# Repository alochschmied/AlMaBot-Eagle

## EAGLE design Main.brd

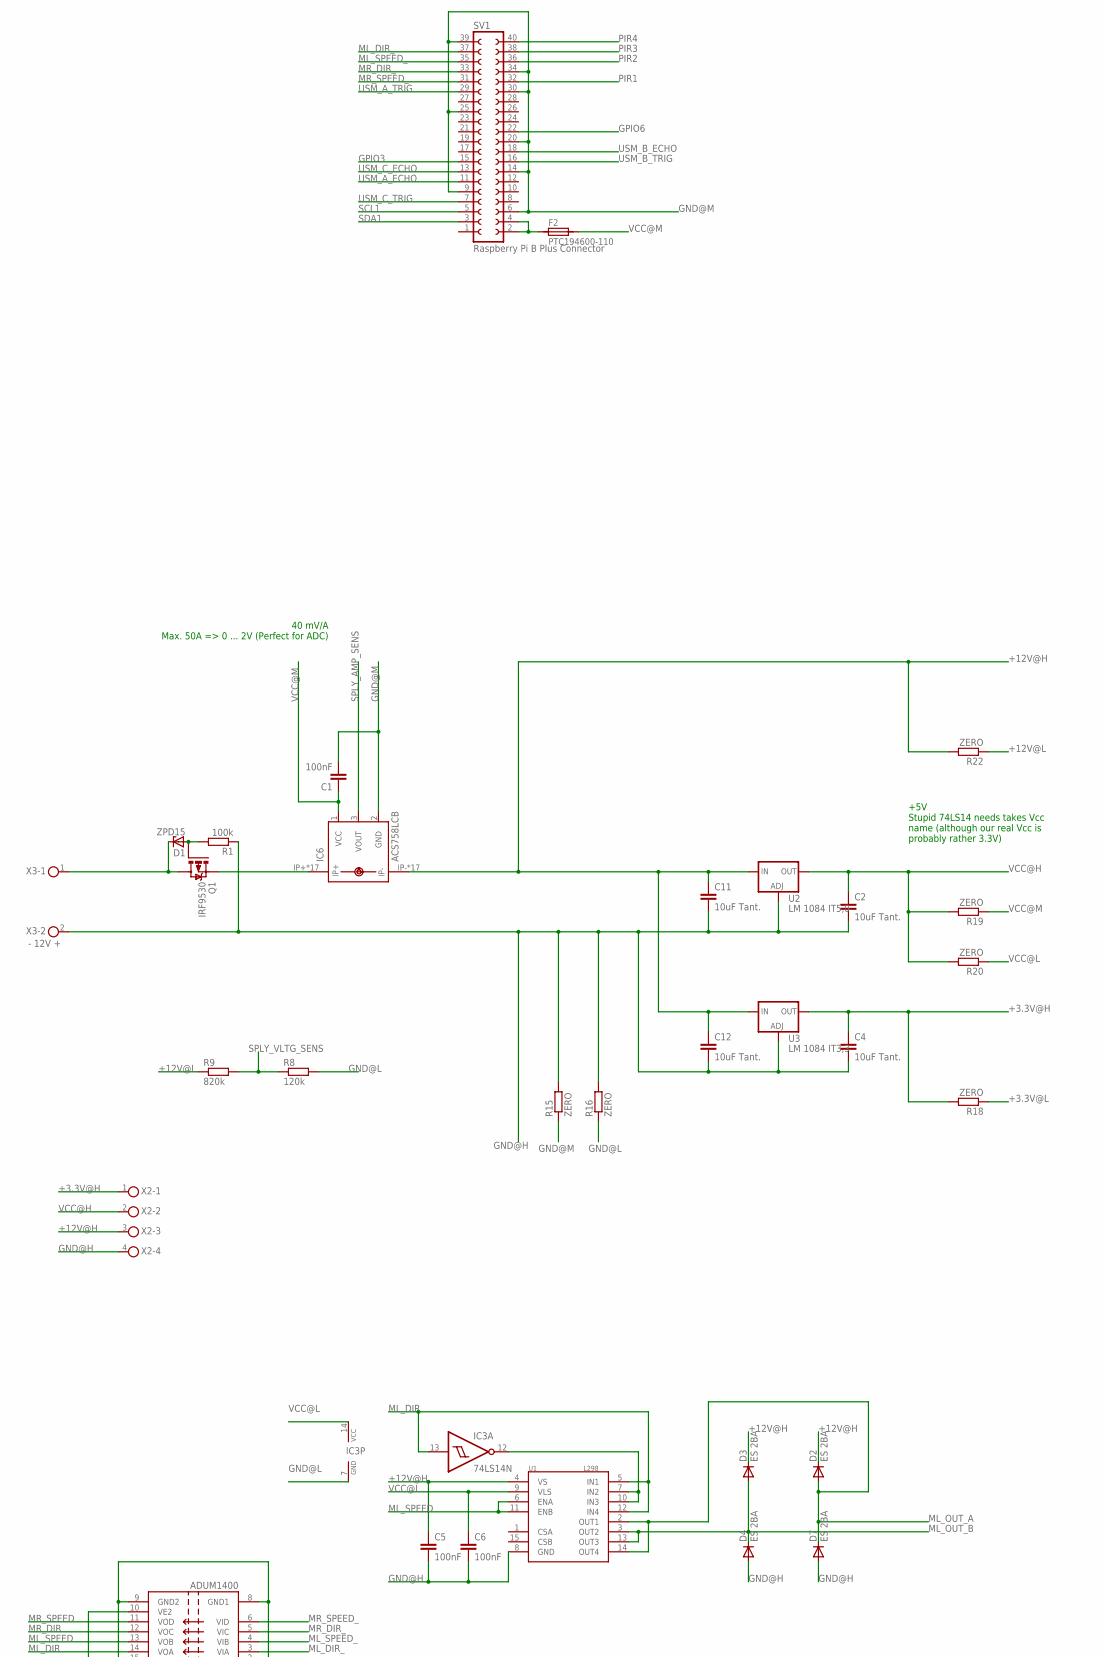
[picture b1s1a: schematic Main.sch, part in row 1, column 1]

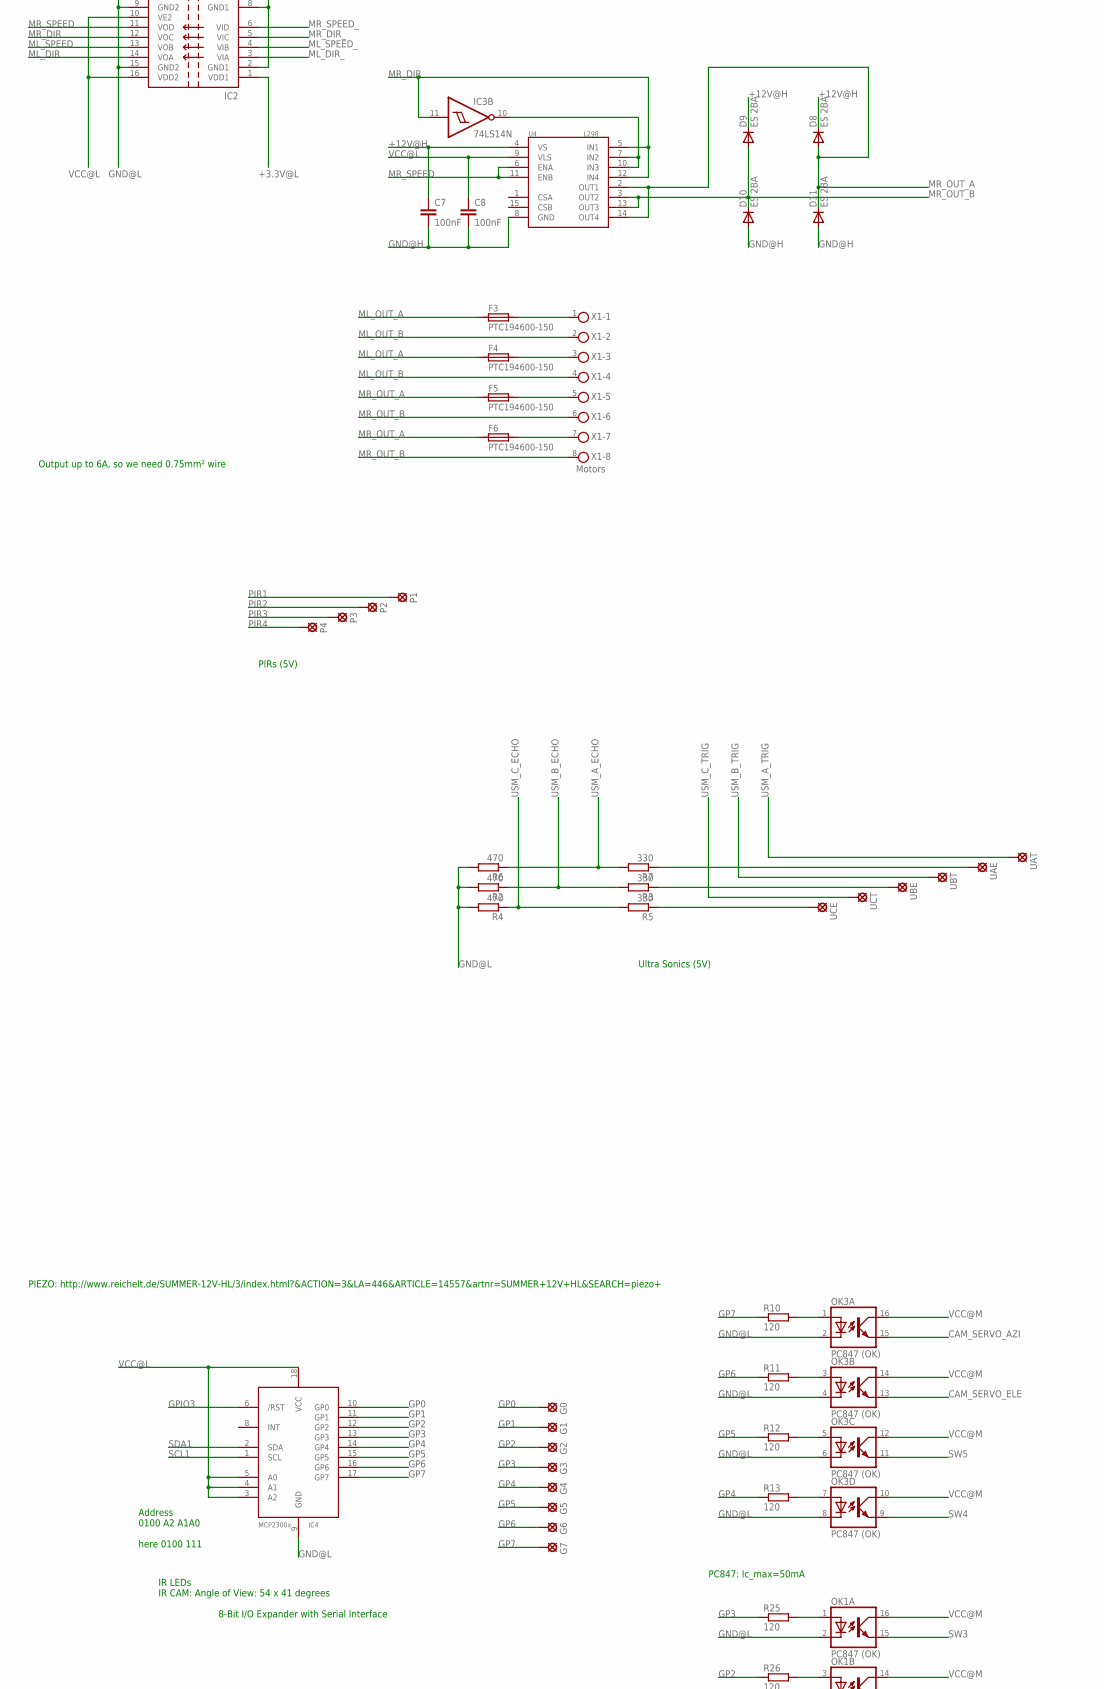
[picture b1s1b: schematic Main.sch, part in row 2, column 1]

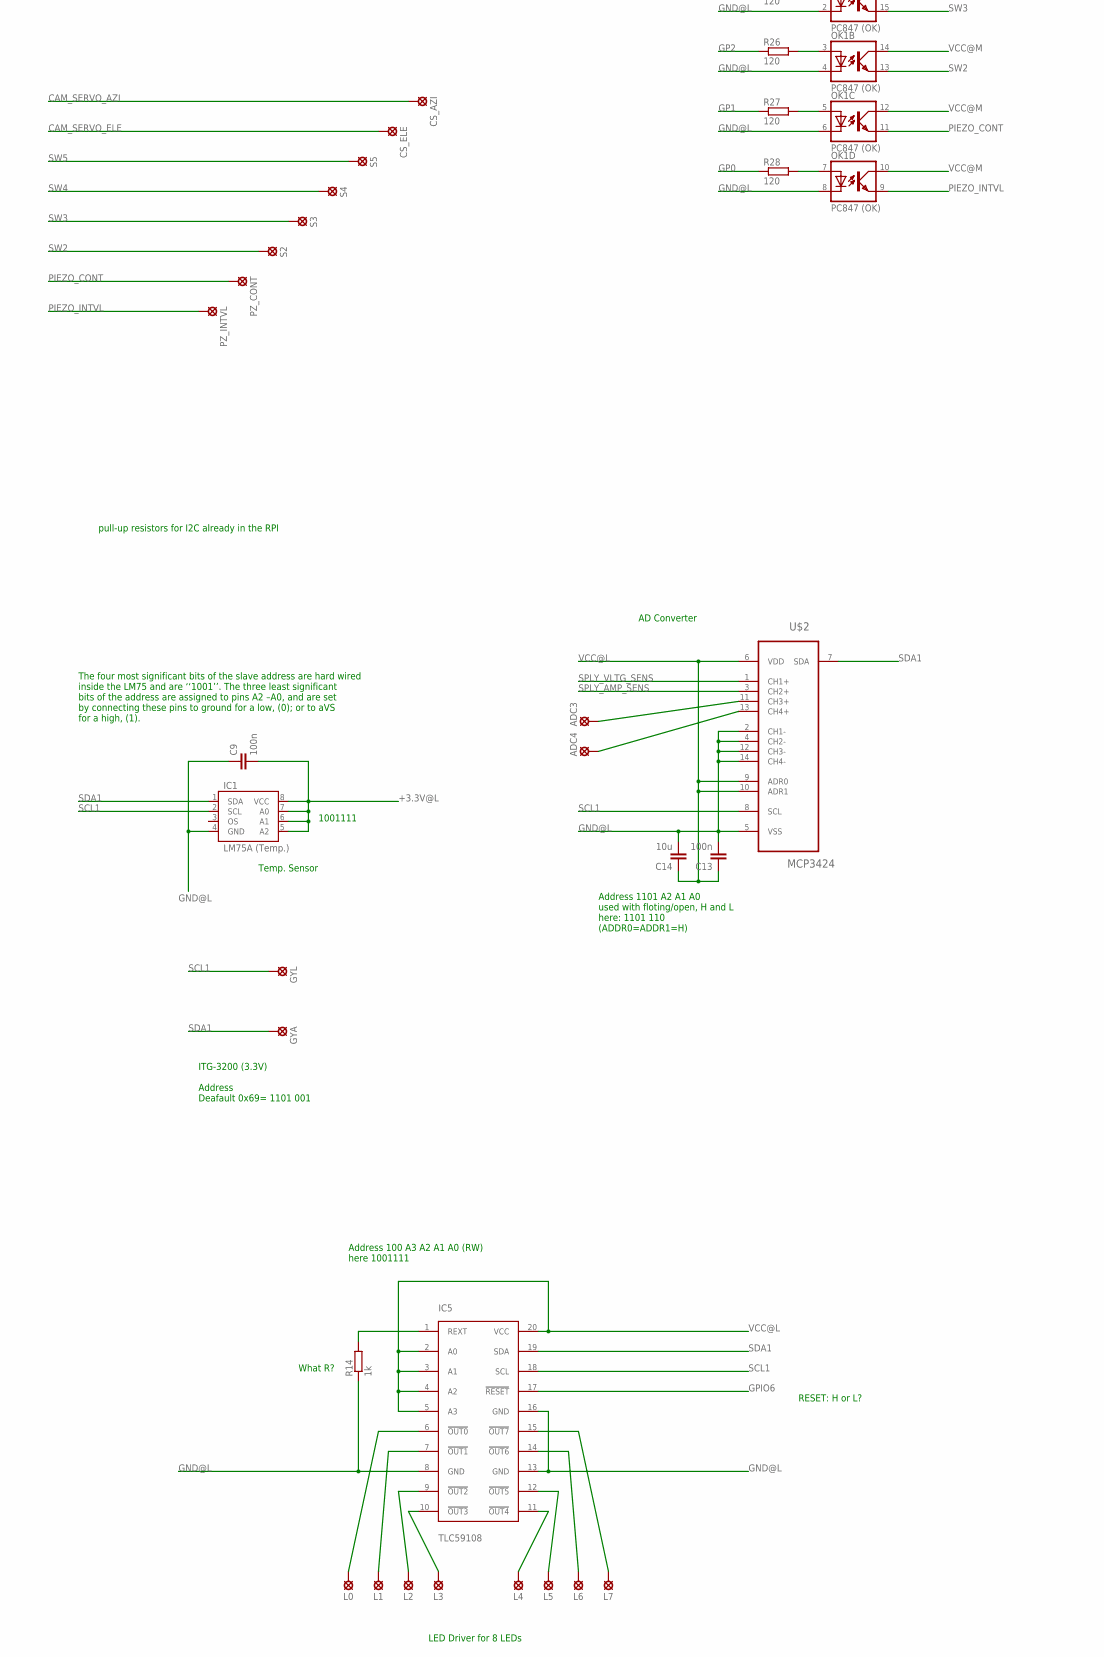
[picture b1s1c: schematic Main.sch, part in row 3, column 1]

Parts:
ADC3, ADC4: LSP10
C1, C5, C6, C7, C8: 100nF; C0805
C2, C4, C11, C12: 10uF Tant.; C025-040X050
C9, C13: 100n; C0805
C14: 10u; C0805
CS_AZI: LSP10
CS_ELE: LSP10
D1: ZPD15; DO35Z10
D2, D3, D4, D7, D8, D9, D10, D11: ES 2BA; SMB
F2: PTC194600-110; 1820
F3, F4, F5, F6: PTC194600-150; 1820
G0, G1, G2, G3, G4, G5, G6, G7: LSP10
GYA: LSP10
GYL: GYRO_SCL; LSP10
IC1: LM75A (Temp.); SO8
IC2: ADUM1400; SO16W
IC3: 74LS14N; DIL14
IC4: MCP2300X/P; DIL18
IC5: TLC59108; TSSOP20
IC6: ACS758LCB; CB-PFF
L0, L1, L2, L3, L4, L5, L6, L7: LSP10
OK1, OK3: PC847 (OK); DIL16
P1, P2, P3, P4: LSP10
PZ_CONT: LSP10
PZ_INTVL: LSP10
Q1: IRF9530; TO220BV
R1: 100k; R0805
R2, R4, R6: 470; R0603
R3, R5, R7: 330; R0603
R8: 120k; R0603
R9: 820k; R0603
R10, R11, R12, R13, R25, R26, R27, R28: 120; R0603
R14: 1k; R0603
R15, R16, R18, R19, R20, R22: ZERO; 0204V
S2, S3, S4, S5: LSP10
SV1: Raspberry Pi B Plus Connector; FE20-2
U1, U4: L298; MULTIWATT15
U2: LM 1084 IT5,0; 317TS
U3: LM 1084 IT3,3; 317TS
U$2: MCP3424; SOP65P640X120-14N
UAE: LSP10
UAT: LSP10
UBE: LSP10
UBT: LSP10
UCE: LSP10
UCT: LSP10
X1: Motors; 8POL35
X2: AKL59-04; 4POL35
X3: - 12V +; 2POL35

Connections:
+3.3V@H: C4.1, R18.2, U3.2 (OUT), X2.1
+3.3V@L: C9.2, IC1.5 (A2), IC1.6 (A1), IC1.7 (A0), IC1.8 (VCC), IC2.1 (VDD1), R18.1
+12V@H: C5.1, C7.1, C11.1, C12.1, D2.C, D3.C, D8.C, D9.C, IC6.IP-, IC6.IP-@2 (IP-), IC6.IP-@3 (IP-), IC6.IP-@4 (IP-), IC6.IP-@5 (IP-), IC6.IP-@6 (IP-), IC6.IP-@7 (IP-), IC6.IP-@8 (IP-), IC6.IP-@9 (IP-), IC6.IP-@10 (IP-), IC6.IP-@11 (IP-), IC6.IP-@12 (IP-), IC6.IP-@13 (IP-), IC6.IP-@14 (IP-), IC6.IP-@15 (IP-), IC6.IP-@16 (IP-), IC6.IP-@17 (IP-), R22.2, U1.4 (VS), U2.3 (IN), U3.3 (IN), U4.4 (VS), X2.3
+12V@L: R9.1, R22.1
CAM_SERVO_AZI: CS_AZI.MP, OK3.15 (EMIT)
CAM_SERVO_ELE: CS_ELE.MP, OK3.13 (EMIT)
GND@H: C2.2, C4.2, C5.2, C6.2, C7.2, C8.2, C11.2, C12.2, D4.A, D7.A, D10.A, D11.A, R1.1, R15.2, R16.2, U1.8 (GND), U2.1 (ADJ), U3.1 (ADJ), U4.8 (GND), X2.4, X3.2
GND@L: C9.1, C13.2, C14.2, IC1.4 (GND), IC2.2 (GND1), IC2.8 (GND1), IC2.9 (GND2), IC2.15 (GND2), IC3.7 (GND), IC4.9 (GND), IC5.8 (GND), IC5.13 (GND), IC5.16 (GND), OK1.2 (C), OK1.4 (C), OK1.6 (C), OK1.8 (C), OK3.2 (C), OK3.4 (C), OK3.6 (C), OK3.8 (C), R2.2, R4.2, R6.2, R8.2, R14.1, R16.1, U$2.2 (CH1-), U$2.4 (CH2-), U$2.5 (VSS), U$2.12 (CH3-), U$2.14 (CH4-)
GND@M: C1.2, IC6.2 (GND), R15.1, SV1.6, SV1.9, SV1.14, SV1.20, SV1.25, SV1.30, SV1.34, SV1.39
GP0: G0.MP, IC4.10 (GP0), R28.1
GP1: G1.MP, IC4.11 (GP1), R27.1
GP2: G2.MP, IC4.12 (GP2), R26.1
GP3: G3.MP, IC4.13 (GP3), R25.1
GP4: G4.MP, IC4.14 (GP4), R13.1
GP5: G5.MP, IC4.15 (GP5), R12.1
GP6: G6.MP, IC4.16 (GP6), R11.1
GP7: G7.MP, IC4.17 (GP7), R10.1
GPIO3: IC4.6 (/RST), SV1.15
GPIO6: IC5.17 (!RESET), SV1.22
ML_B: IC3.12 (O), U1.7 (IN2), U1.10 (IN3)
ML_DIR: IC2.14 (VOA), IC3.13 (I), U1.5 (IN1), U1.12 (IN4)
ML_DIR_: IC2.3 (VIA), SV1.37
ML_OUT_A: D2.A, D7.C, F3.1, F4.1, U1.2 (OUT1), U1.14 (OUT4)
ML_OUT_B: D3.A, D4.C, U1.3 (OUT2), U1.13 (OUT3), X1.2, X1.4
ML_SPEED: IC2.13 (VOB), U1.6 (ENA), U1.11 (ENB)
ML_SPEED_: IC2.4 (VIB), SV1.35
MR_B: IC3.10 (O), U4.7 (IN2), U4.10 (IN3)
MR_DIR: IC2.12 (VOC), IC3.11 (I), U4.5 (IN1), U4.12 (IN4)
MR_DIR_: IC2.5 (VIC), SV1.33
MR_OUT_A: D8.A, D11.C, F5.1, F6.1, U4.2 (OUT1), U4.14 (OUT4)
MR_OUT_B: D9.A, D10.C, U4.3 (OUT2), U4.13 (OUT3), X1.6, X1.8
MR_SPEED: IC2.11 (VOD), U4.6 (ENA), U4.11 (ENB)
MR_SPEED_: IC2.6 (VID), SV1.31
unnamed: IC5.1 (REXT), R14.2
unnamed: D1.A, Q1.G, R1.2
unnamed: D1.C, Q1.D, X3.1
unnamed: F2.1, SV1.2, SV1.4
unnamed: IC5.11 (!OUT4), L4.MP
unnamed: F3.2, X1.1
unnamed: IC5.10 (!OUT3), L3.MP
unnamed: IC5.9 (!OUT2), L2.MP
unnamed: OK3.1 (A), R10.2
unnamed: ADC3.MP, U$2.11 (CH3+)
unnamed: OK3.3 (A), R11.2
unnamed: R7.1, UAE.MP
unnamed: OK3.5 (A), R12.2
unnamed: R3.1, UBE.MP
unnamed: OK3.7 (A), R13.2
unnamed: F4.2, X1.3
unnamed: IC5.7 (!OUT1), L1.MP
unnamed: IC5.6 (!OUT0), L0.MP
unnamed: IC5.15 (!OUT7), L7.MP
unnamed: IC5.14 (!OUT6), L6.MP
unnamed: R5.1, UCE.MP
unnamed: F5.2, X1.5
unnamed: F6.2, X1.7
unnamed: IC5.12 (!OUT5), L5.MP
unnamed: OK1.1 (A), R25.2
unnamed: OK1.3 (A), R26.2
unnamed: OK1.5 (A), R27.2
unnamed: OK1.7 (A), R28.2
unnamed: IC6.IP+, IC6.IP+@2 (IP+), IC6.IP+@3 (IP+), IC6.IP+@4 (IP+), IC6.IP+@5 (IP+), IC6.IP+@6 (IP+), IC6.IP+@7 (IP+), IC6.IP+@8 (IP+), IC6.IP+@9 (IP+), IC6.IP+@10 (IP+), IC6.IP+@11 (IP+), IC6.IP+@12 (IP+), IC6.IP+@13 (IP+), IC6.IP+@14 (IP+), IC6.IP+@15 (IP+), IC6.IP+@16 (IP+), IC6.IP+@17 (IP+), Q1.S
unnamed: ADC4.MP, U$2.13 (CH4+)
PIEZO_CONT: OK1.11 (EMIT), PZ_CONT.MP
PIEZO_INTVL: OK1.9 (EMIT), PZ_INTVL.MP
PIR1: P1.MP, SV1.32
PIR2: P2.MP, SV1.36
PIR3: P3.MP, SV1.38
PIR4: P4.MP, SV1.40
SCL1: GYL.MP, IC1.2 (SCL), IC4.1 (SCL), IC5.18 (SCL), SV1.5, U$2.8 (SCL)
SDA1: GYA.MP, IC1.1 (SDA), IC4.2 (SDA), IC5.19 (SDA), SV1.3, U$2.7 (SDA)
SPLY_AMP_SENS: IC6.3 (VOUT), U$2.3 (CH2+)
SPLY_VLTG_SENS: R8.1, R9.2, U$2.1 (CH1+)
SW2: OK1.13 (EMIT), S2.MP
SW3: OK1.15 (EMIT), S3.MP
SW4: OK3.9 (EMIT), S4.MP
SW5: OK3.11 (EMIT), S5.MP
USM_A_ECHO: R6.1, R7.2, SV1.11
USM_A_TRIG: SV1.29, UAT.MP
USM_B_ECHO: R2.1, R3.2, SV1.18
USM_B_TRIG: SV1.16, UBT.MP
USM_C_ECHO: R4.1, R5.2, SV1.13
USM_C_TRIG: SV1.7, UCT.MP
VCC@H: C2.1, R19.2, R20.2, U2.2 (OUT), X2.2
VCC@L: C6.1, C8.1, C13.1, C14.1, IC2.10 (VE2), IC2.16 (VDD2), IC3.14 (VCC), IC4.3 (A2), IC4.4 (A1), IC4.5 (A0), IC4.18 (VCC), IC5.2 (A0), IC5.3 (A1), IC5.4 (A2), IC5.5 (A3), IC5.20 (VCC), R20.1, U1.9 (VLS), U4.9 (VLS), U$2.6 (VDD), U$2.9 (ADR0), U$2.10 (ADR1)
VCC@M: C1.1, F2.2, IC6.1 (VCC), OK1.10 (COL), OK1.12 (COL), OK1.14 (COL), OK1.16 (COL), OK3.10 (COL), OK3.12 (COL), OK3.14 (COL), OK3.16 (COL), R19.1

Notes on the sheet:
Output up to 6A, so we need 0.75mm² wire
pull-up resistors for I2C already in the RPI
The four most significant bits of the slave address are hard wired inside the LM75 and are ‘‘1001’’. The three least significant bits of the address are assigned to pins A2 –A0, and are set by connecting these pins to ground for a low, (0); or to aVS for a high, (1).
1001111
+5V Stupid 74LS14 needs takes Vcc name (although our real Vcc is probably rather 3.3V)
Address 0100 A2 A1A0 here 0100 111
ITG-3200 (3.3V) Address Deafault 0x69= 1101 001
Address 100 A3 A2 A1 A0 (RW) here 1001111
RESET: H or L?
What R?
PC847: Ic_max=50mA
PIEZO: http://www.reichelt.de/SUMMER-12V-HL/3/index.html?&ACTION=3&LA=446&ARTICLE=14557&artnr=SUMMER+12V+HL&SEARCH=piezo+
Ultra Sonics (5V)
PIRs (5V)
40 mV/A Max. 50A => 0 ... 2V (Perfect for ADC)
Address 1101 A2 A1 A0 used with floting/open, H and L here: 1101 110 (ADDR0=ADDR1=H)
IR LEDs IR CAM: Angle of View: 54 x 41 degrees
LED Driver for 8 LEDs
AD Converter
Temp. Sensor
8-Bit I/O Expander with Serial Interface

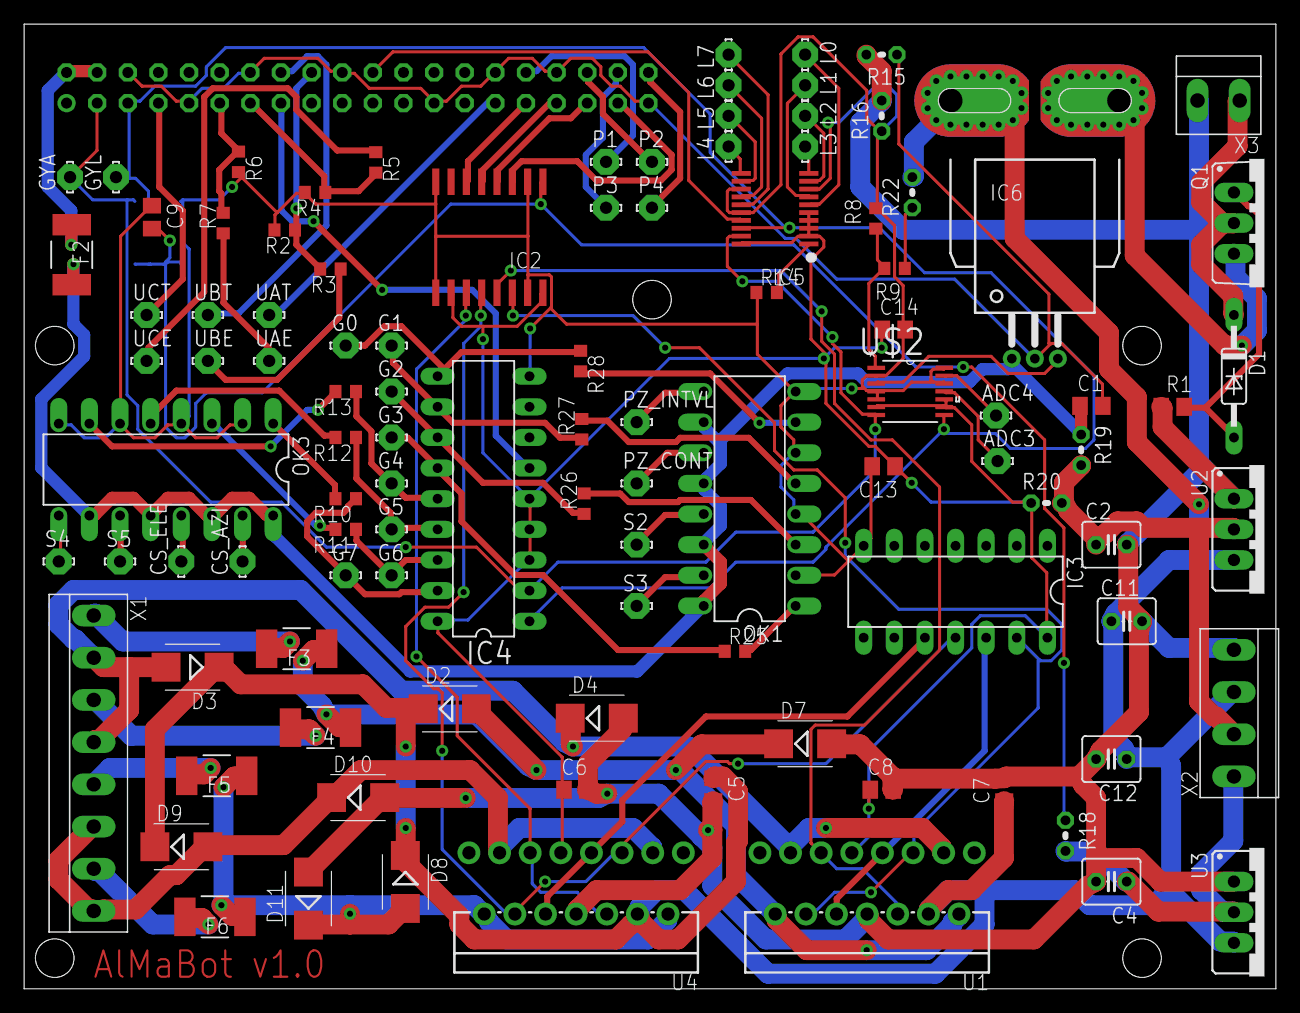
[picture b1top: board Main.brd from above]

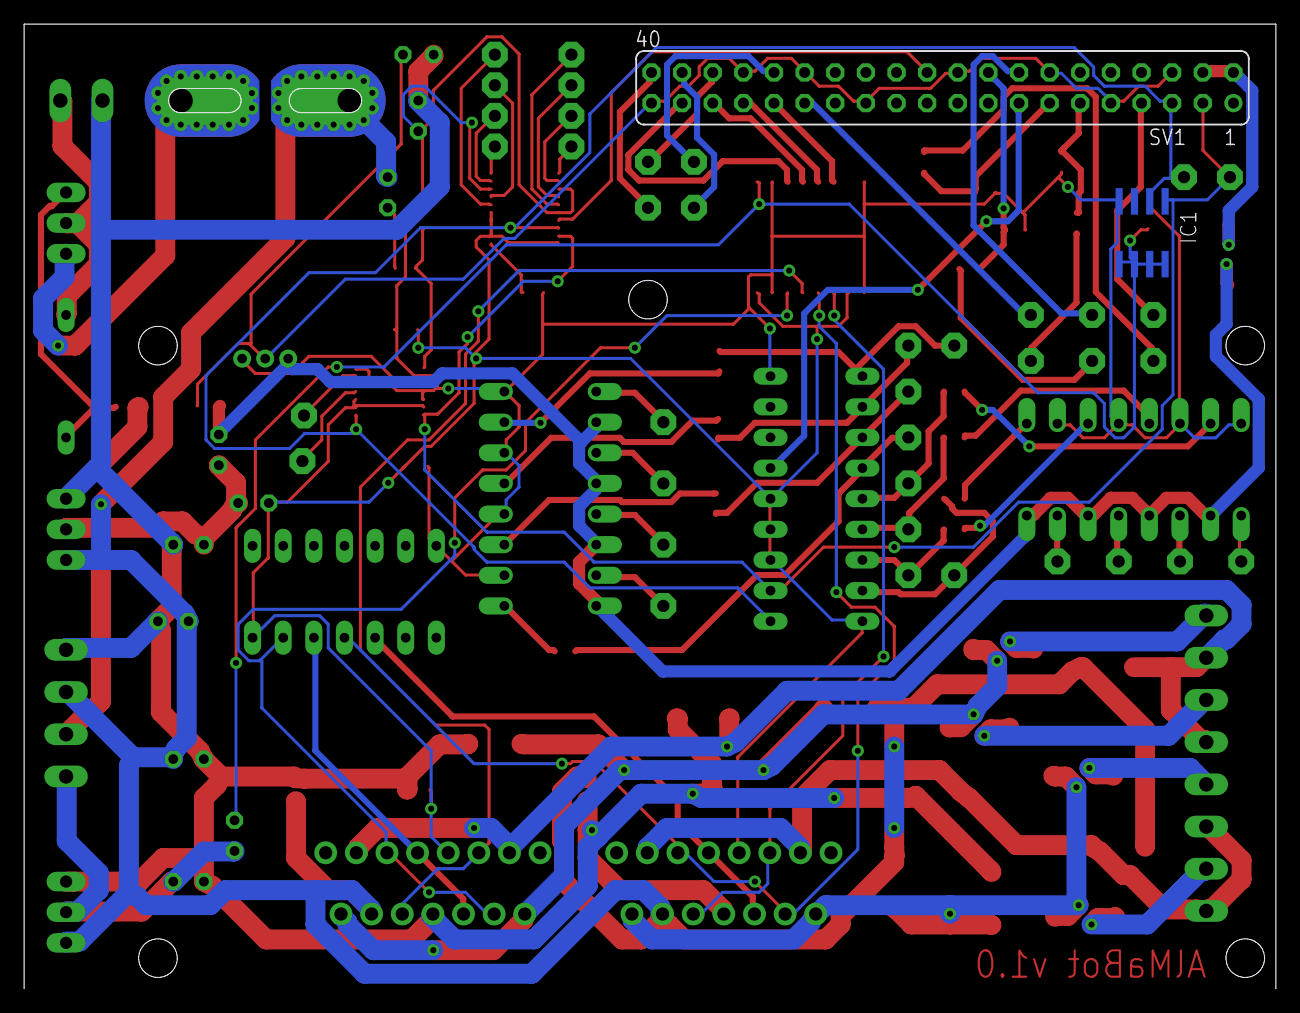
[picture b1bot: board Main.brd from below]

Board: 2 copper layers, 103.8 x 80.0 mm, 106 parts (2 on the bottom side), 86 nets.

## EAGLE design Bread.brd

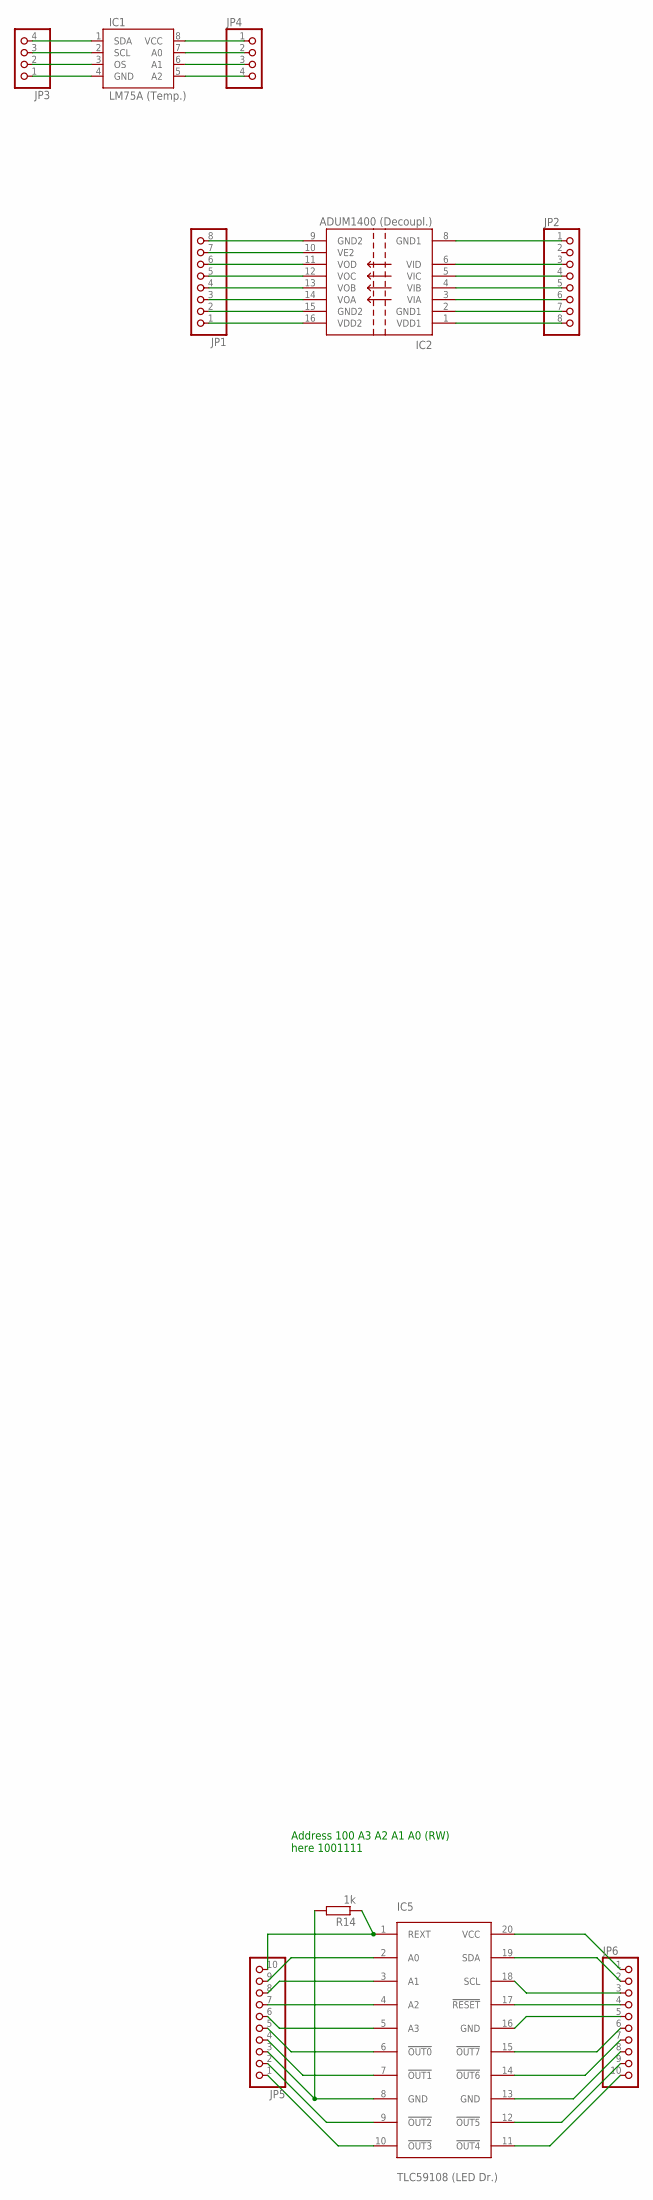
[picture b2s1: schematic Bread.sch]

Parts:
IC1: LM75A (Temp.); SO8
IC2: ADUM1400 (Decoupl.); SO16W
IC5: TLC59108 (LED Dr.); TSSOP20
JP1, JP2: PINHD-1X8_2.54; 1X08
JP3, JP4: PINHD-1X4_2.54; 1X04
JP5, JP6: PINHD-1X10_2.54; 1X10
R14: 1k; R0603

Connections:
GND1@1: IC2.2 (GND1), JP2.7
GND1@2: IC2.8 (GND1), JP2.1
GND2@1: IC2.15 (GND2), JP1.2
GND2@2: IC2.9 (GND2), JP1.8
unnamed: IC5.1 (REXT), JP5.10, R14.1
unnamed: IC2.10 (VE2), JP1.7
unnamed: IC2.11 (VOD), JP1.6
unnamed: IC2.12 (VOC), JP1.5
unnamed: IC2.13 (VOB), JP1.4
unnamed: IC5.2 (A0), JP5.9
unnamed: IC2.14 (VOA), JP1.3
unnamed: IC5.3 (A1), JP5.8
unnamed: IC2.16 (VDD2), JP1.1
unnamed: IC2.6 (VID), JP2.3
unnamed: IC2.5 (VIC), JP2.4
unnamed: IC5.4 (A2), JP5.7
unnamed: IC2.4 (VIB), JP2.5
unnamed: IC2.3 (VIA), JP2.6
unnamed: IC2.1 (VDD1), JP2.8
unnamed: IC1.1 (SDA), JP3.4
unnamed: IC1.2 (SCL), JP3.3
unnamed: IC1.3 (OS), JP3.2
unnamed: IC1.4 (GND), JP3.1
unnamed: IC1.8 (VCC), JP4.1
unnamed: IC1.7 (A0), JP4.2
unnamed: IC1.6 (A1), JP4.3
unnamed: IC1.5 (A2), JP4.4
unnamed: IC5.5 (A3), JP5.6
unnamed: IC5.6 (!OUT0), JP5.5
unnamed: IC5.7 (!OUT1), JP5.4
unnamed: IC5.8 (GND), JP5.3, R14.2
unnamed: IC5.9 (!OUT2), JP5.2
unnamed: IC5.10 (!OUT3), JP5.1
unnamed: IC5.20 (VCC), JP6.1
unnamed: IC5.19 (SDA), JP6.2
unnamed: IC5.18 (SCL), JP6.3
unnamed: IC5.17 (!RESET), JP6.4
unnamed: IC5.16 (GND), JP6.5
unnamed: IC5.15 (!OUT7), JP6.6
unnamed: IC5.14 (!OUT6), JP6.7
unnamed: IC5.13 (GND), JP6.8
unnamed: IC5.12 (!OUT5), JP6.9
unnamed: IC5.11 (!OUT4), JP6.10

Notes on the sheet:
Address 100 A3 A2 A1 A0 (RW) here 1001111

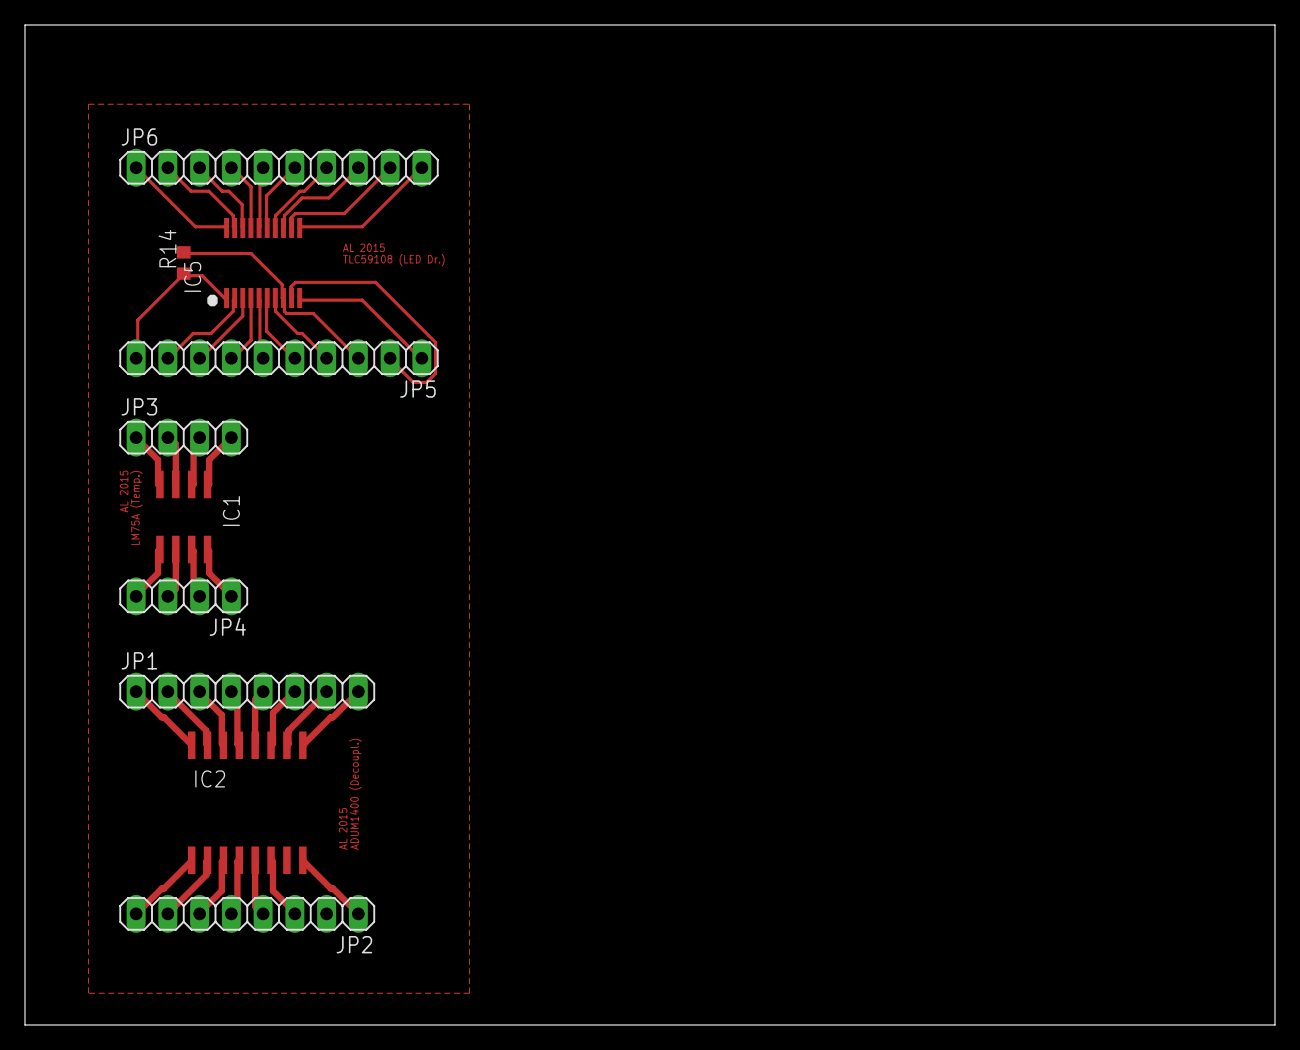
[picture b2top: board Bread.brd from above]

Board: 1 copper layer, 100.0 x 80.0 mm, 10 parts (0 on the bottom side), 43 nets.

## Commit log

2014-12-08 Initial checking with just a few unwired components
2014-12-09 added motor using basic pins AK500
2014-12-09 ignoring my push script
2014-12-09 added first version of power supply
2014-12-10 restructured with scratchpad
2014-12-10 playing with board
2014-12-10 got rid of unneeded junctions
2014-12-10 got rid of more unneeded junctions
2014-12-10 fixed it... misleading warnings due to unneeded wires
2014-12-10 got rid of hopefully redundant C
2014-12-11 finally got connections without wires
2014-12-11 added first motor driver
2014-12-12 added second motor driver and fixed protction diodes
2014-12-12 some routing experiments
2014-12-12 using ria screw terminals
2014-12-12 got board working again
2014-12-12 better protection for reverse polarity
2014-12-13 added PIRs
2014-12-13 connections to RPI
2014-12-13 some cleanup
2014-12-13 fuses
2014-12-13 added 2 ultrasonic sensors
2014-12-14 a third ultrasonic sensor
2014-12-14 temperatur and humidity sensor
2014-12-20 optimizing GPIO usage; more I2C; protected RPI from L298
2014-12-20 played with routing
2014-12-20 replaced ADC
2014-12-21 added voltage monitor and replaced protction diodes
2014-12-21 playing with routes
2014-12-23 cleanup and started to add servo control
2014-12-23 optimizing board
2014-12-23 smd protection diodes for h bridge
2014-12-23 gpio expander
2014-12-23 100% route
2014-12-25 placed Cs closer to corresponding parts
2014-12-25 cleanup and notes
2014-12-25 more output switches
2014-12-26 reafctoring LEDs control
2014-12-28 improved net thicknesses
2014-12-28 fixed some errors
2014-12-28 moreoutputs
2014-12-29 started workon current sensor
2014-12-29 current sensor
2014-12-29 thicker wires
2014-12-29 pin names
2014-12-29 moved parts
2014-12-29 better GPIO usage
2015-01-07 saving progress?
2015-01-07 bread
2015-01-22 mirrored layout
2016-03-12 Added PDF
2016-03-12 Added PDF for board
2016-10-05 Before upgrade of Eagle
2016-10-06 Review
2016-10-07 Iter
2016-10-08 Done?
2016-11-04 This is versionI ordered :-)

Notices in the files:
parts and their libraries:
SparkFun-PowerIC: Licensing: Creative Commons ShareAlike 4.0 International - https://creativecommons.org/licenses/by-sa/4.0
